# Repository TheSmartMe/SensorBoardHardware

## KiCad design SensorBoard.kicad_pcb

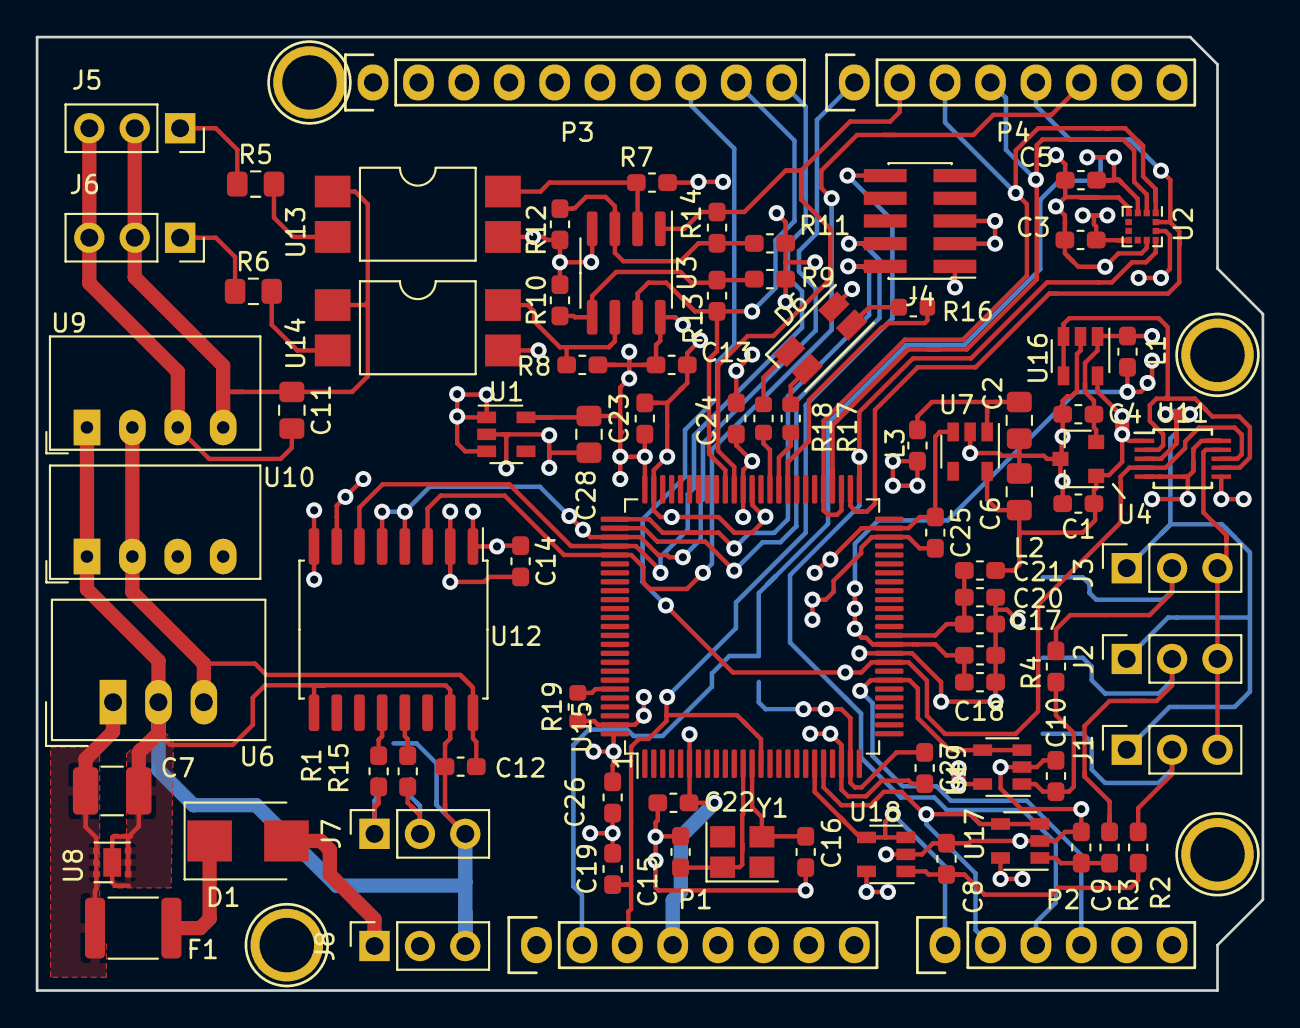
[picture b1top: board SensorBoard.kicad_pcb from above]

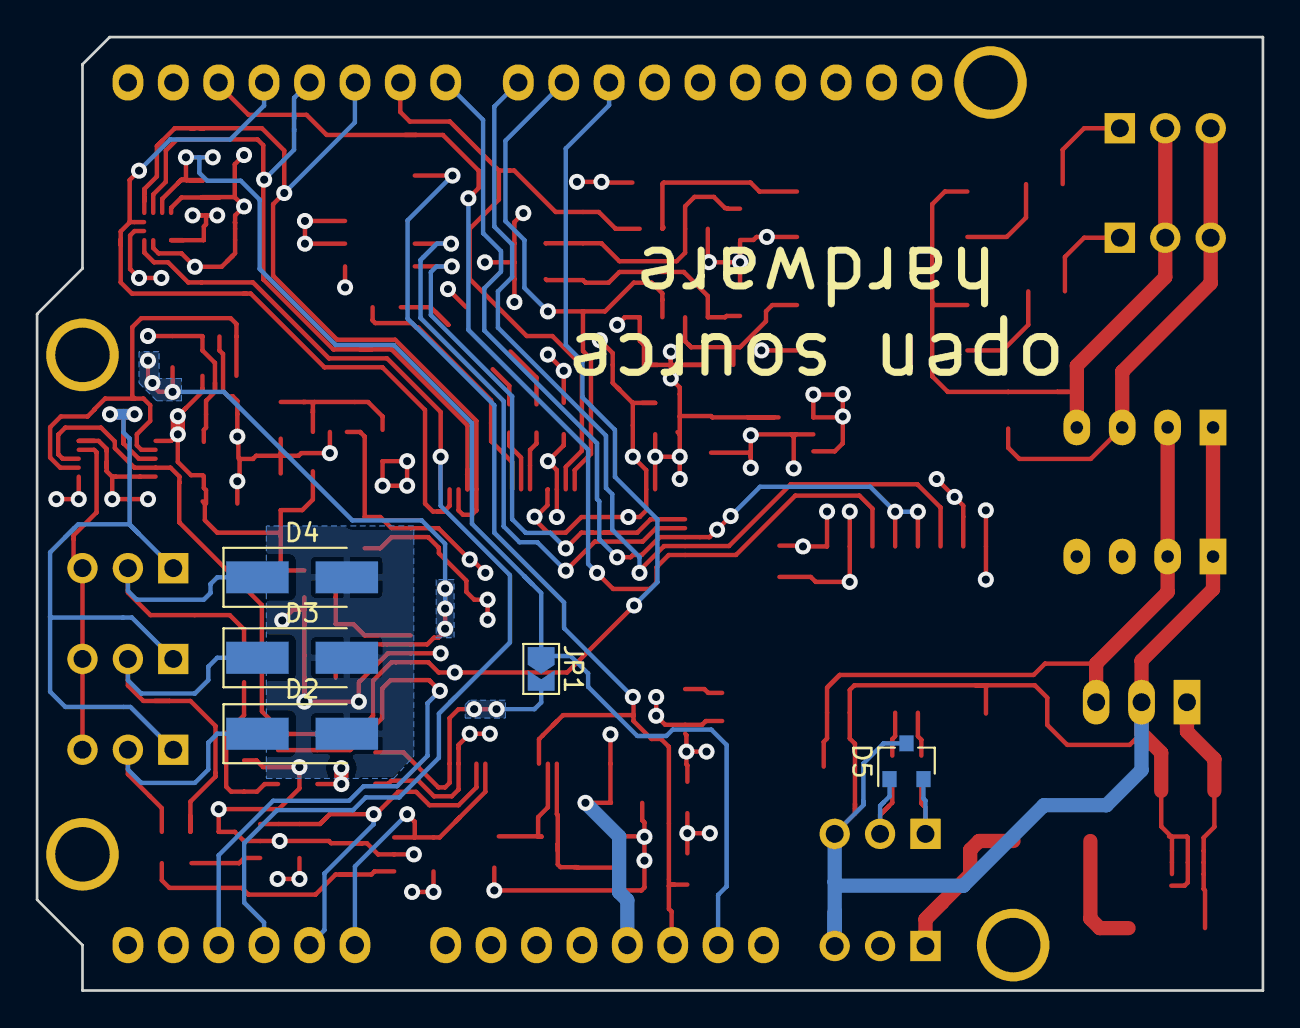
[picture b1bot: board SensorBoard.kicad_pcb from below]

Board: 4 copper layers, 68.6 x 53.3 mm, 93 parts (5 on the bottom side), 62 nets.

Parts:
C1, C3, C4, C5, C8, C9, C10, C12, C13, C14: C_Small; C_0603_1608Metric_Pad1.05x0.95mm_HandSolder
C2, C6, C11: C_Small; C_0805_2012Metric_Pad1.15x1.40mm_HandSolder
C7: C_Small; C_1210_3225Metric_Pad1.42x2.65mm_HandSolder
C15, C16: 12pF; C_0603_1608Metric_Pad1.05x0.95mm_HandSolder
C17, C19, C20, C22, C23, C24, C25, C26, C27: 100nF; C_0603_1608Metric_Pad1.05x0.95mm_HandSolder
C18, C21: 1u; C_0603_1608Metric_Pad1.05x0.95mm_HandSolder
C28: 4.7u; C_0805_2012Metric_Pad1.15x1.40mm_HandSolder
D1: B260; D_SMB
D2, D3, D4: SMAJ5.0A; D_SMA_Handsoldering
D5: SM712_SOT23; SOT-23
D6: LED_RGBC; LED_RGB_1210
F1: Polyfuse; R_1812_4532Metric
J1, J2, J3, J5, J6, J7, J8: Conn_01x03_Male; PinSocket_1x03_P2.54mm_Vertical
J4: Conn_02x05_Odd_Even; PinHeader_2x05_P1.27mm_Vertical_SMD
JP1: SolderJumper_2_Bridged; SolderJumper-2_P1.3mm_Open_TrianglePad1.0x1.5mm
L1, L2, L3: 600R@100MHz; L_0603_1608Metric_Pad1.05x0.95mm_HandSolder
P1: Power; Socket_Strip_Arduino_1x08
P2: Analog; Socket_Strip_Arduino_1x06
P3: Digital; Socket_Strip_Arduino_1x10
P4: Digital; Socket_Strip_Arduino_1x08
P5, P6, P7, P8: CONN_01X01; Arduino_1pin
R1, R2, R3, R4, R7, R8, R9, R10, R11, R12, R13, R14, R15: R_Small; R_0603_1608Metric_Pad1.05x0.95mm_HandSolder
R5, R6: R_Small; R_0805_2012Metric_Pad1.15x1.40mm_HandSolder
R16, R17, R18, R19: R_Small; R_0603_1608Metric
U1: TPS76333; SOT-23-5
U2: KX022-1020; LGA-12_2x2mm_P0.5mm
U3: LM2903; SOIC-8_3.9x4.9mm_P1.27mm
U4: REF3025; SOT-23
U6: TSR_1-2450; Converter_DCDC_TRACO_TSR-1_THT
U7: TPS76330; SOT-23-5
U8: TVS3300DRV; WSON-6-1EP_2x2mm_P0.65mm_EP1x1.6mm
U9: TME0509S; Converter_DCDC_TRACO_TMExxxxS_THT
U10: TME0505S; Converter_DCDC_TRACO_TMExxxxS_THT
U11: TS3A24159DGSR; TSSOP-10_3x3mm_P0.5mm
U12: ADM2486xRW; SOIC-16W_7.5x10.3mm_P1.27mm
U13, U14: LTV-817S; SMDIP-4_W9.53mm
U15: STM32G431VBTx; LQFP-100_14x14mm_P0.5mm
U16, U17, U18, U19: LMV321; SOT-23-5
Y1: Crystal_GND24; Crystal_SMD_Abracon_ABM8G-4Pin_3.2x2.5mm

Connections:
+3V3: C13.1, C14.1, C22.1, C23.1, C24.1, C25.1, C26.1, C27.1, C28.1, J4.1, JP1.2, P1.4, R7.1, R8.2, R9.1, R11.1, U1.5, U3.8, U7.3, U12.1, U12.7, U15.6, U15.24, U15.49, U15.64, U15.75, U15.100
+5V: L3.2, P1.5, U1.1, U1.3, U10.4
+5VD: C12.1, U6.3, U9.2, U10.2, U12.16
/2(RX): P4.6, U12.3, U15.80
/3(SCK): P4.5, U2.12, U15.52
/4(MOSI): P4.4, U2.2, U15.54
/5(MISO): P4.3, U2.1, U15.53, U15.55
/6(RPM1): P4.2, R14.2, U3.1, U15.65
/7(DE): P4.1, U12.4, U12.5, U15.78
/8(TX): P3.10, U12.6, U15.79
/9(RPM2): P3.9, R13.2, U3.7, U15.66
/10(**/SS): P3.8, U11.4, U11.8, U15.34
/A: D5.2, J7.1, R1.2
/A0: P2.1, U15.20, U18.3, U18.4
/A1: P2.2, U15.21, U17.3, U17.4
/A2(SS): P2.3, U2.10, U15.51
/A3: P2.4, U15.32, U19.3, U19.4
/AREF: C4.1, L1.1, P3.3, U4.2, U16.1
/B: D5.1, J7.2, R15.2
/EX: J1.1, J2.1, J3.1, U11.3
/IOREF: C5.1, JP1.1, P1.2, U2.3
/RVCC: C11.1, J5.2, J6.2, U9.4, U13.1, U14.1
/Reset: C19.1, J4.10, P1.3, U15.14
/SensorBoardCPU/B: R16.2, U15.59
/SensorBoardCPU/G: R17.2, U15.60
/SensorBoardCPU/R: R18.2, U15.61
/SensorBoardCPU/SWCLK: J4.4, U15.77
/SensorBoardCPU/SWDIO: J4.2, U15.76
/VIN: D1.2, J8.1
/nEX: J1.3, J2.3, J3.3, U11.9
GND: C1.2, C2.2, C3.2, C4.2, C5.2, C6.2, C8.2, C9.2, C10.2, C13.2, C14.2, C15.1, C16.1, C17.2, C18.2, C19.2, C20.2, C21.2, C22.2, C23.2, C24.2, C25.2, C26.2, C27.2, C28.2, D2.2, D3.2, D4.2, D6.4, J4.3, J4.5, P1.6, P1.7, P3.4, R10.2, R12.2, R19.1, U1.2, U2.4, U2.9, U2.11, U3.4, U4.3, U7.2, U10.3, U11.5, U11.6, U11.10, U12.2, U12.8, U13.3, U14.3, U15.23, U15.35, U15.48, U15.63, U15.74, U15.99, U16.2, U17.2, U18.2, U19.2
GNDA: C11.2, J5.3, J6.3, U9.3
GNDD: C7.2, C12.2, D5.3, J7.3, J8.3, U6.2, U8.1, U8.2, U8.3, U8.7, U9.1, U10.1, U12.9, U12.15
unnamed: C2.1, L3.1, U7.1
unnamed: C7.1, F1.1, U6.1, U8.4, U8.5, U8.6
unnamed: C8.1, R2.2, U18.1
unnamed: C9.1, R3.2, U17.1
unnamed: C10.1, R4.2, U19.1
unnamed: C15.2, U15.12, Y1.1
unnamed: C16.2, U15.13, Y1.3
unnamed: C17.1, C18.1, L1.2, U15.36
unnamed: C20.1, C21.1, L2.1, U15.37
unnamed: D1.1, F1.2
unnamed: D2.1, J1.2, R2.1
unnamed: D3.1, J2.2, R3.1
unnamed: D4.1, J3.2, R4.1
unnamed: D6.1, R18.1
unnamed: D6.2, R17.1
unnamed: D6.3, R16.1
unnamed: J5.1, R5.1
unnamed: J6.1, R6.1
unnamed: R1.1, U12.12
unnamed: R5.2, U13.2
unnamed: R6.2, U14.2
unnamed: R7.2, U3.2, U13.4
unnamed: R8.1, U3.6, U14.4
unnamed: R9.2, R10.1, R13.1, U3.5
unnamed: R11.2, R12.1, R14.1, U3.3
unnamed: R15.1, U12.13
unnamed: R19.2, U15.95
unnamed: U11.2, U11.7, U16.3, U16.4
VDDA: C1.1, C3.1, C6.1, L2.2, U2.7, U4.1, U7.5, U11.1, U16.5, U17.5, U18.5, U19.5

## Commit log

2021-04-21 Initial commit for sensor board
